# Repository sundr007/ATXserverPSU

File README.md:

# ATXserverPSU

ATX computer power supply utilizing redundant server power supplies for mining applications.
The Server power supplies will converter AC to 12Vdc with high efficiency.
The ATXs box will then take that 12V, create 5V and 3.3V, supply the needed logic and then provide a modular ATX connector set to connect to the mother board, graphics cards, etc.

The biggest benefit of this system is that the server power supplies will provide very high output power at high efficiency.

The circuit boards are done in KiCAD.
The mechanicals are done in OpenSCAD.

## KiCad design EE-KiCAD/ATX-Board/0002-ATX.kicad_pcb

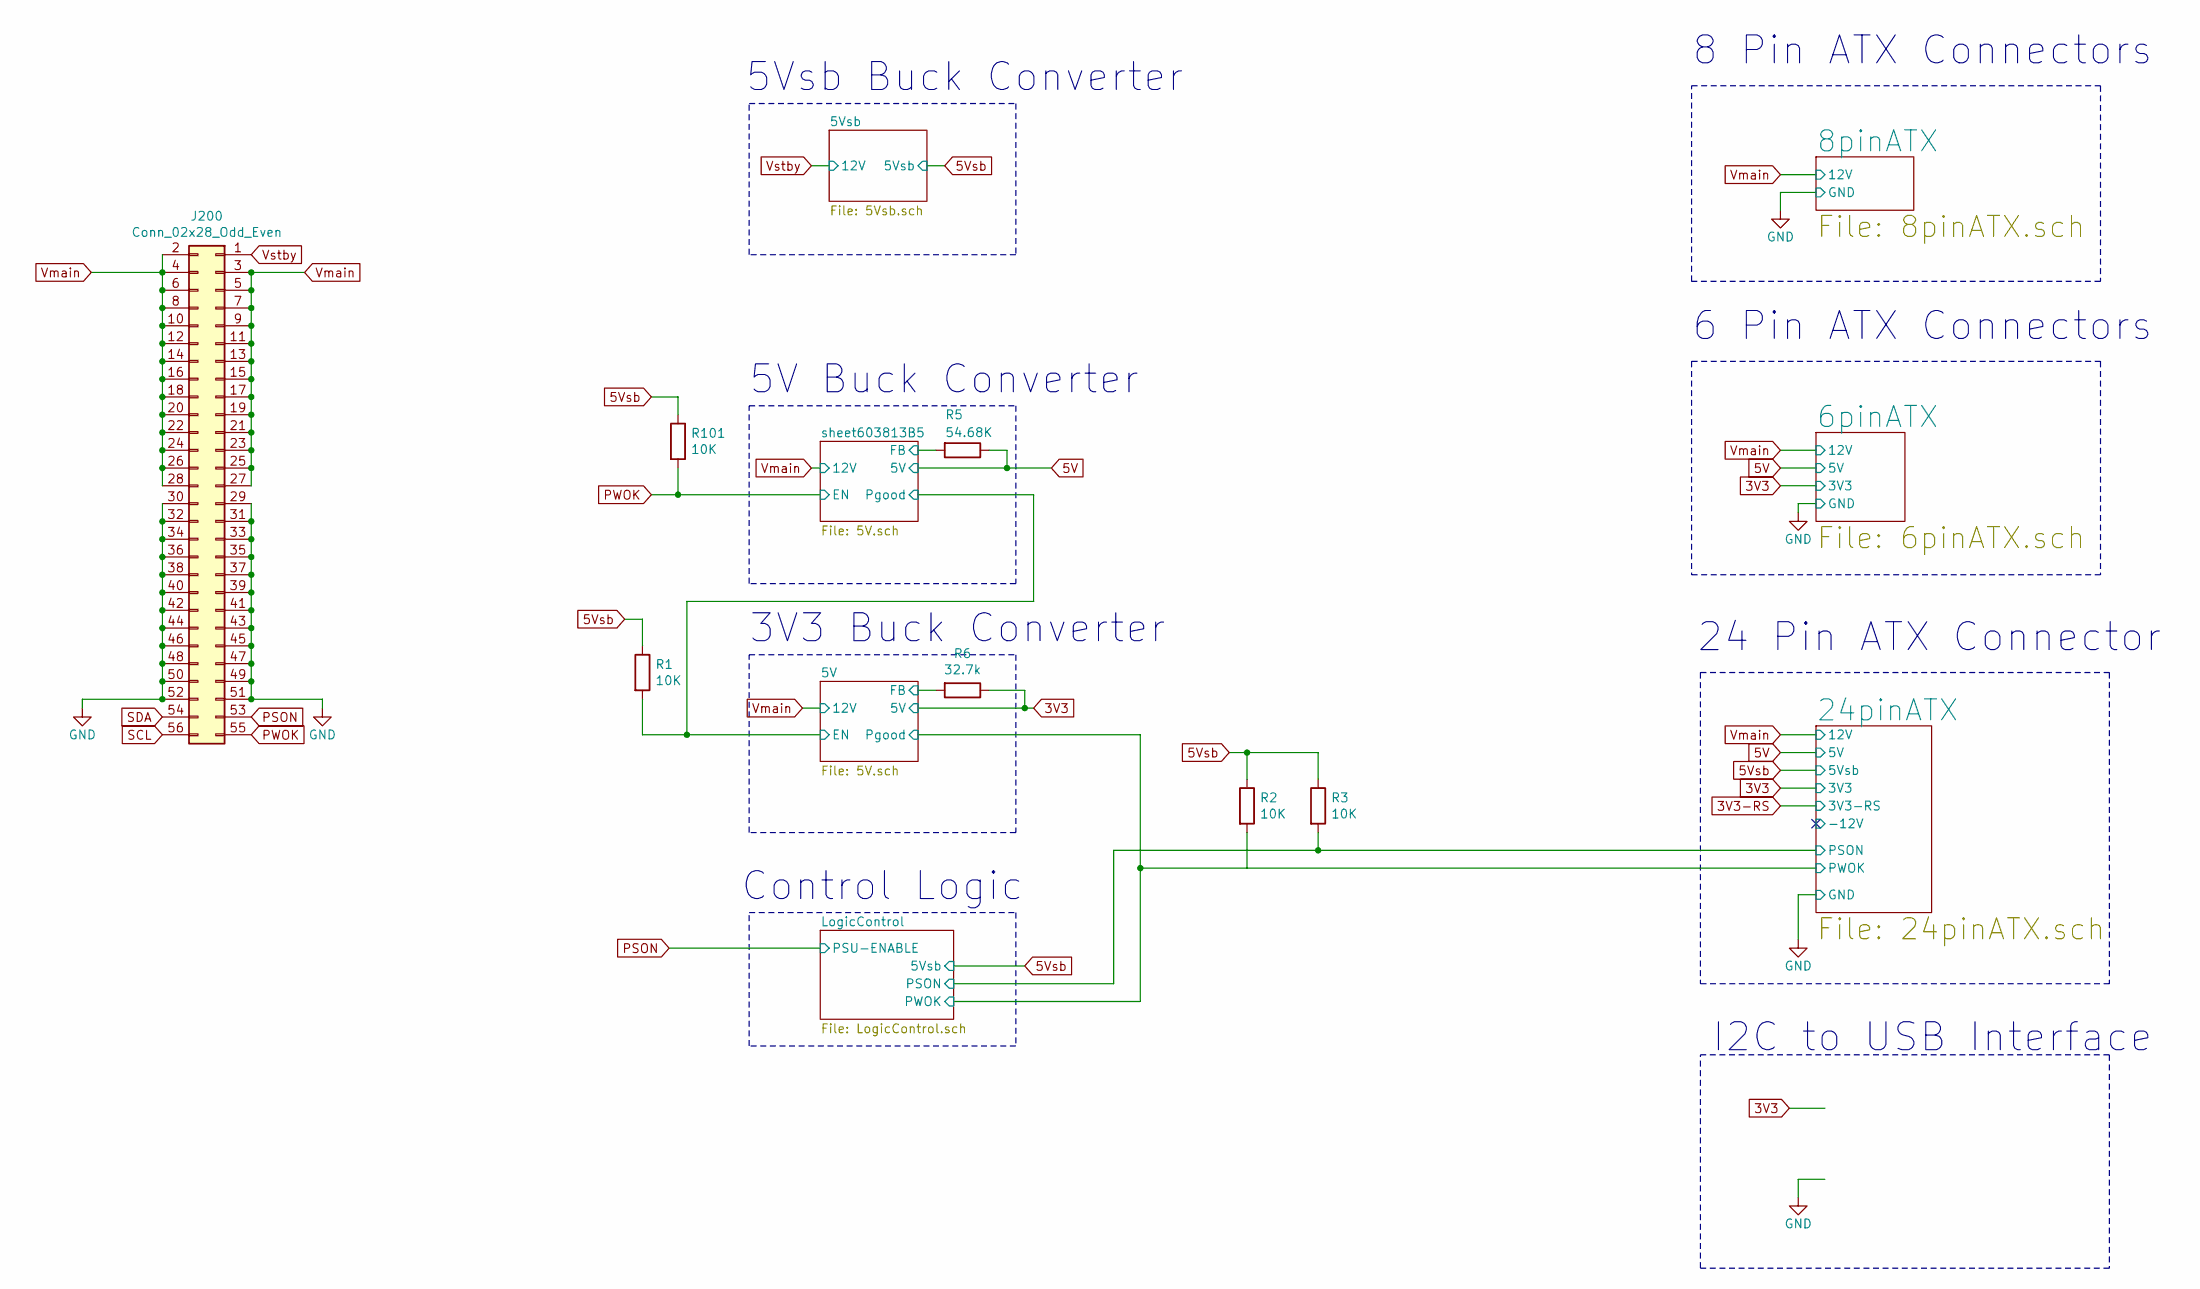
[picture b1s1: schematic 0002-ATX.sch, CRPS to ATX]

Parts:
J200: Conn_02x28_Odd_Even; PinSocket_2x28_P2.54mm_Horizontal
R1, R2, R3, R101: 10K; 0805_R
R5: 54.68K; 0805_R
R6: 32.7k; 0805_R

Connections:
3V3: R6.1; also elsewhere on the board
5V: R5.1; also elsewhere on the board
5Vsb: R1.1, R2.1, R3.1, R101.1; also elsewhere on the board
/5V/EN: R1.2; also elsewhere on the board
/5V/FB: R6.2; also elsewhere on the board
/24pinATX/PSON: R3.2; also elsewhere on the board
/sheet603813B5/FB: R5.2; also elsewhere on the board
GND: J200.29, J200.30, J200.31, J200.32, J200.33, J200.34, J200.35, J200.36, J200.37, J200.38, J200.39, J200.40, J200.41, J200.42, J200.43, J200.44, J200.45, J200.46, J200.47, J200.48, J200.49, J200.50, J200.51, J200.52; also elsewhere on the board
PSON: J200.53; also elsewhere on the board
PWOK: J200.55, R101.2; also elsewhere on the board
SCL: J200.56
SDA: J200.54
Vmain: J200.2, J200.3, J200.4, J200.5, J200.6, J200.7, J200.8, J200.9, J200.10, J200.11, J200.12, J200.13, J200.14, J200.15, J200.16, J200.17, J200.18, J200.19, J200.20, J200.21, J200.22, J200.23, J200.24, J200.25, J200.26, J200.27, J200.28; also elsewhere on the board
Vstby: J200.1; also elsewhere on the board

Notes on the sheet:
8 Pin ATX Connectors
6 Pin ATX Connectors
24 Pin ATX Connector
5Vsb Buck Converter
5V Buck Converter
3V3 Buck Converter
Control Logic
I2C to USB Interface

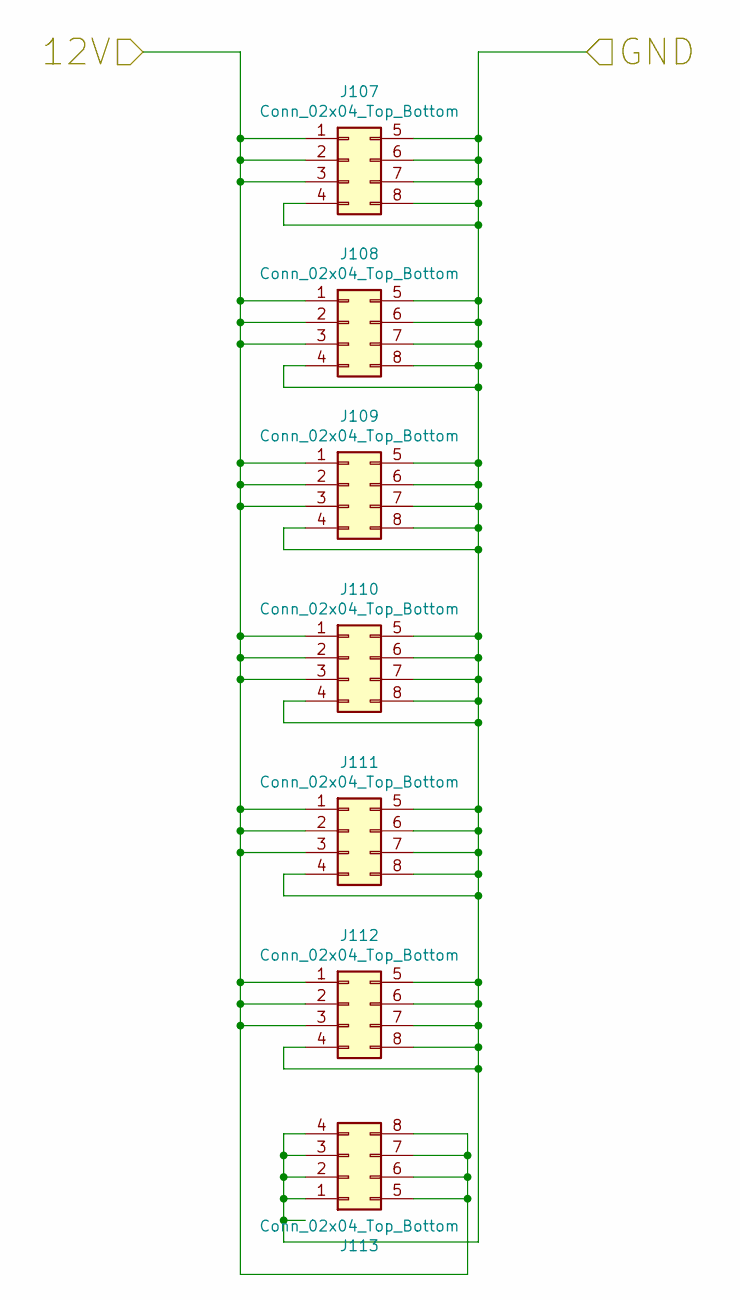
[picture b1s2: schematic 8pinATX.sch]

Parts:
J107, J108, J109, J110, J111, J112, J113: Conn_02x04_Top_Bottom; Molex_Mini-Fit_Jr_5566-08A_2x04_P4.20mm_Vertical

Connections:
GND: J107.4, J107.5, J107.6, J107.7, J107.8, J108.4, J108.5, J108.6, J108.7, J108.8, J109.4, J109.5, J109.6, J109.7, J109.8, J110.4, J110.5, J110.6, J110.7, J110.8, J111.4, J111.5, J111.6, J111.7, J111.8, J112.4, J112.5, J112.6, J112.7, J112.8, J113.1, J113.2, J113.3, J113.4; also elsewhere on the board
Vmain: J107.1, J107.2, J107.3, J108.1, J108.2, J108.3, J109.1, J109.2, J109.3, J110.1, J110.2, J110.3, J111.1, J111.2, J111.3, J112.1, J112.2, J112.3, J113.5, J113.6, J113.7, J113.8; also elsewhere on the board

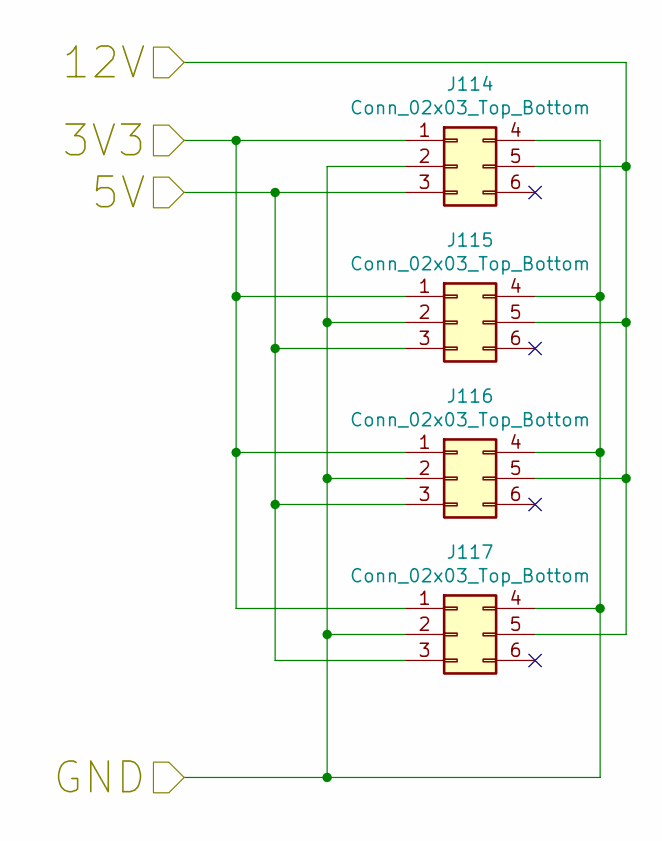
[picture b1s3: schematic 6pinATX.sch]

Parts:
J114, J115, J116, J117: Conn_02x03_Top_Bottom; Molex_Mini-Fit_Jr_5566-06A_2x03_P4.20mm_Vertical

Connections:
3V3: J114.1, J115.1, J116.1, J117.1; also elsewhere on the board
5V: J114.3, J115.3, J116.3, J117.3; also elsewhere on the board
GND: J114.2, J114.4, J115.2, J115.4, J116.2, J116.4, J117.2, J117.4; also elsewhere on the board
Vmain: J114.5, J115.5, J116.5, J117.5; also elsewhere on the board

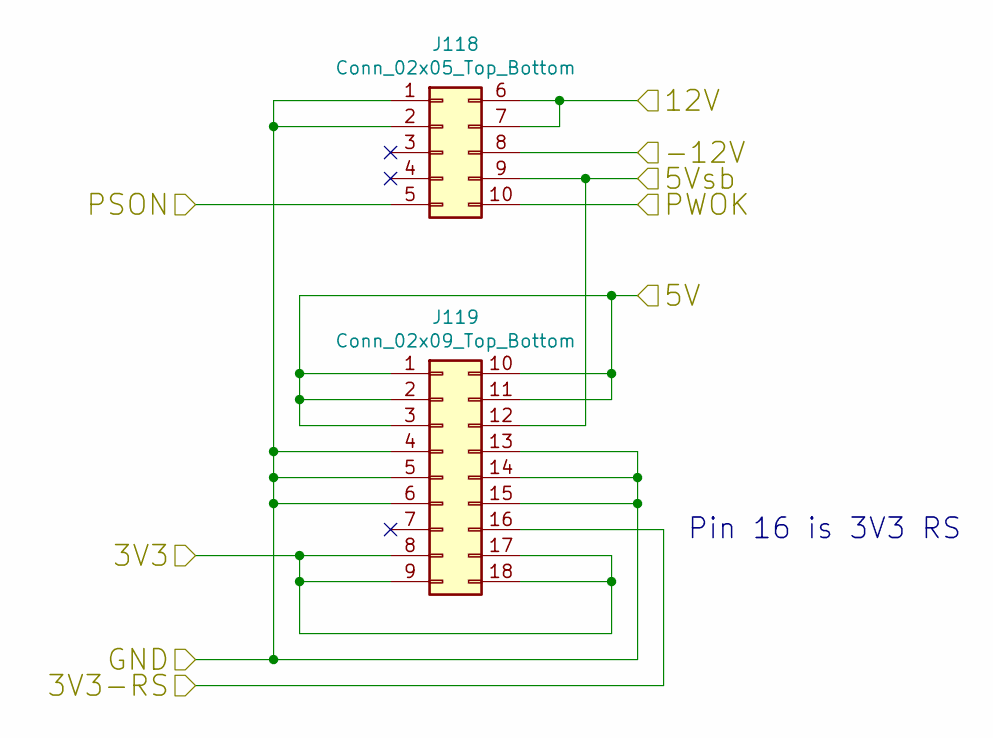
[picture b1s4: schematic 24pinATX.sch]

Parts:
J118: Conn_02x05_Top_Bottom; Molex_Mini-Fit_Jr_5566-10A_2x05_P4.20mm_Vertical
J119: Conn_02x09_Top_Bottom; Molex_Mini-Fit_Jr_5566-18A_2x09_P4.20mm_Vertical

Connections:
3V3: J119.8, J119.9, J119.17, J119.18; also elsewhere on the board
3V3-RS: J119.16
5V: J119.1, J119.2, J119.3, J119.10, J119.11; also elsewhere on the board
5Vsb: J118.9, J119.12; also elsewhere on the board
/24pinATX/-12V: J118.8
/24pinATX/PSON: J118.5; also elsewhere on the board
/24pinATX/PWOK: J118.10; also elsewhere on the board
GND: J118.1, J118.2, J119.4, J119.5, J119.6, J119.13, J119.14, J119.15; also elsewhere on the board
Vmain: J118.6, J118.7; also elsewhere on the board

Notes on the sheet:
Pin 16 is 3V3 RS

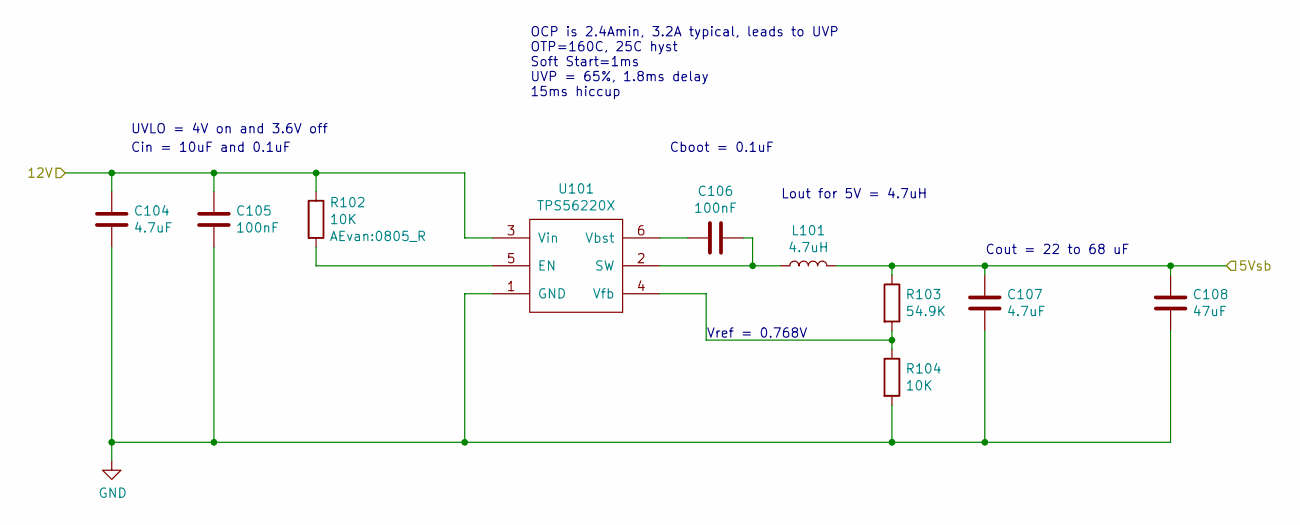
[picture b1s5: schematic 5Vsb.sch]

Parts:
C104, C107: 4.7uF; 0805_C
C105, C106: 100nF; 0805_C
C108: 47uF; CP_EIA-3528-15_AVX-H; Digikey_PN 718-2167-1-ND
L101: 4.7uH; L_6.3x6.3_H3
R102, R104: 10K; 0805_R
R103: 54.9K; 0805_R
U101: TPS56220X; SOT-23-6_Handsoldering

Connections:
5Vsb: C107.1, C108.1, L101.2, R103.1; also elsewhere on the board
GND: C104.2, C105.2, C107.2, C108.2, R104.2, U101.1 (GND); also elsewhere on the board
unnamed: C106.1, L101.1, U101.2 (SW)
unnamed: C106.2, U101.6 (Vbst)
unnamed: R102.2, U101.5 (EN)
unnamed: R103.2, R104.1, U101.4 (Vfb)
Vstby: C104.1, C105.1, R102.1, U101.3 (Vin); also elsewhere on the board

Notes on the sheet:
Cin = 10uF and 0.1uF
UVLO = 4V on and 3.6V off
Vref = 0.768V
Cboot = 0.1uF
Lout for 5V = 4.7uH
Cout = 22 to 68 uF
OCP is 2.4Amin, 3.2A typical, leads to UVP OTP=160C, 25C hyst Soft Start=1ms UVP = 65%, 1.8ms delay 15ms hiccup

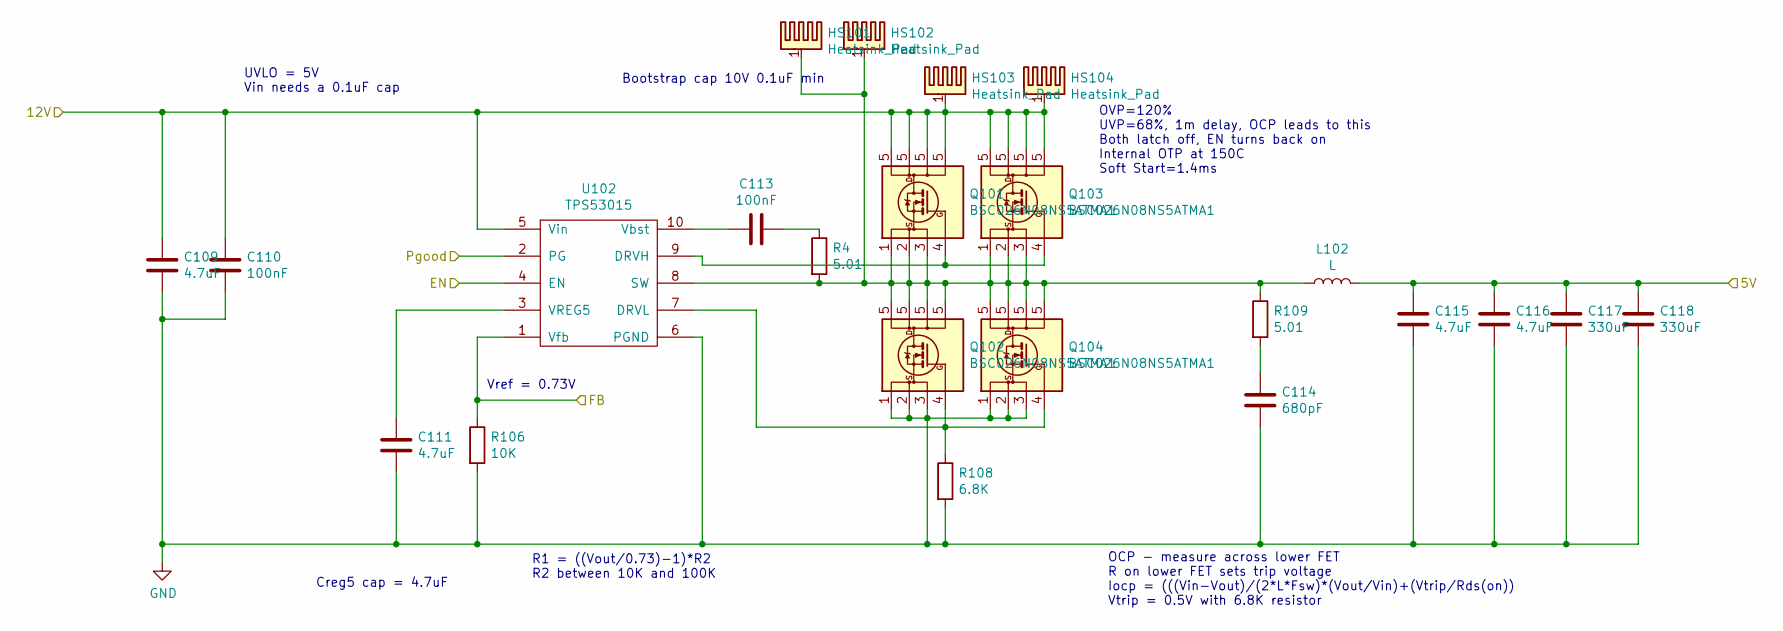
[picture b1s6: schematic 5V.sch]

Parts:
C109, C111, C115, C116: 4.7uF; 0805_C
C110, C113: 100nF; 0805_C
C114: 680pF; 0805_C
C117, C118: 330uF; C_Radial_D6.3mm_H7.0mm_P2.50mm
HS101, HS102, HS103, HS104: Heatsink_Pad; 5X6-HEATSINK
L102: L; L_12x12mm_H8mm
Q101, Q102, Q103, Q104: BSC026N08NS5ATMA1; TDSON-8-1
R4, R109: 5.01; 0805_R
R106: 10K; 0805_R
R108: 6.8K; 0805_R
U102: TPS53015; VSSOP-10_2.4x2.1mm_Pitch0.5mm

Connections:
3V3: C115.1, C116.1, C117.1, C118.1, L102.2; also elsewhere on the board
/5V/EN: U102.4 (EN); also elsewhere on the board
/5V/FB: R106.1, U102.1 (Vfb); also elsewhere on the board
/24pinATX/PWOK: U102.2 (PG); also elsewhere on the board
GND: C109.2, C110.2, C111.2, C114.2, C115.2, C116.2, C117.2, C118.2, Q102.1 (S), Q102.2 (S), Q102.3 (S), Q104.1 (S), Q104.2 (S), Q104.3 (S), R106.2, R108.2, U102.6 (PGND); also elsewhere on the board
unnamed: C111.1, U102.3 (VREG5)
unnamed: C113.1, R4.1
unnamed: C113.2, U102.10 (Vbst)
unnamed: C114.1, R109.2
unnamed: HS101.1, HS102.1, L102.1, Q101.1 (S), Q101.2 (S), Q101.3 (S), Q102.5 (D), Q103.1 (S), Q103.2 (S), Q103.3 (S), Q104.5 (D), R4.2, R109.1, U102.8 (SW)
unnamed: Q101.4 (G), Q103.4 (G), U102.9 (DRVH)
unnamed: Q102.4 (G), Q104.4 (G), R108.1, U102.7 (DRVL)
Vmain: C109.1, C110.1, HS103.1, HS104.1, Q101.5 (D), Q103.5 (D), U102.5 (Vin); also elsewhere on the board

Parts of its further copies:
C2, C4, C7, C8: 4.7uF; 0805_C
C3, C5: 100nF; 0805_C
C6: 680pF; 0805_C
C9, C10: 330uF; C_Radial_D6.3mm_H7.0mm_P2.50mm
HS1, HS2, HS3, HS4: Heatsink_Pad; 5X6-HEATSINK
L1: L; L_12x12mm_H8mm
Q1, Q2, Q3, Q4: BSC026N08NS5ATMA1; TDSON-8-1
R10: 10K; 0805_R
R11, R13: 5.01; 0805_R
R12: 6.8K; 0805_R
U1: TPS53015; VSSOP-10_2.4x2.1mm_Pitch0.5mm

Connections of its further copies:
5V: C7.1, C8.1, C9.1, C10.1, L1.2; also elsewhere on the board
/5V/EN: U1.2 (PG); also elsewhere on the board
/sheet603813B5/FB: R10.1, U1.1 (Vfb); also elsewhere on the board
GND: C2.2, C3.2, C4.2, C6.2, C7.2, C8.2, C9.2, C10.2, Q2.1 (S), Q2.2 (S), Q2.3 (S), Q4.1 (S), Q4.2 (S), Q4.3 (S), R10.2, R12.2, U1.6 (PGND); also elsewhere on the board
unnamed: C4.1, U1.3 (VREG5)
unnamed: C5.1, R11.1
unnamed: C5.2, U1.10 (Vbst)
unnamed: C6.1, R13.2
unnamed: HS1.1, HS2.1, L1.1, Q1.1 (S), Q1.2 (S), Q1.3 (S), Q2.5 (D), Q3.1 (S), Q3.2 (S), Q3.3 (S), Q4.5 (D), R11.2, R13.1, U1.8 (SW)
unnamed: Q1.4 (G), Q3.4 (G), U1.9 (DRVH)
unnamed: Q2.4 (G), Q4.4 (G), R12.1, U1.7 (DRVL)
PWOK: U1.4 (EN); also elsewhere on the board
Vmain: C2.1, C3.1, HS3.1, HS4.1, Q1.5 (D), Q3.5 (D), U1.5 (Vin); also elsewhere on the board

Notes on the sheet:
OVP=120% UVP=68%, 1m delay, OCP leads to this Both latch off, EN turns back on Internal OTP at 150C Soft Start=1.4ms
Bootstrap cap 10V 0.1uF min
UVLO = 5V Vin needs a 0.1uF cap
Creg5 cap = 4.7uF
R1 = ((Vout/0.73)-1)*R2 R2 between 10K and 100K
Vref = 0.73V
OCP - measure across lower FET R on lower FET sets trip voltage Iocp = (((Vin-Vout)/(2*L*Fsw)*(Vout/Vin)+(Vtrip/Rds(on)) Vtrip = 0.5V with 6.8K resistor

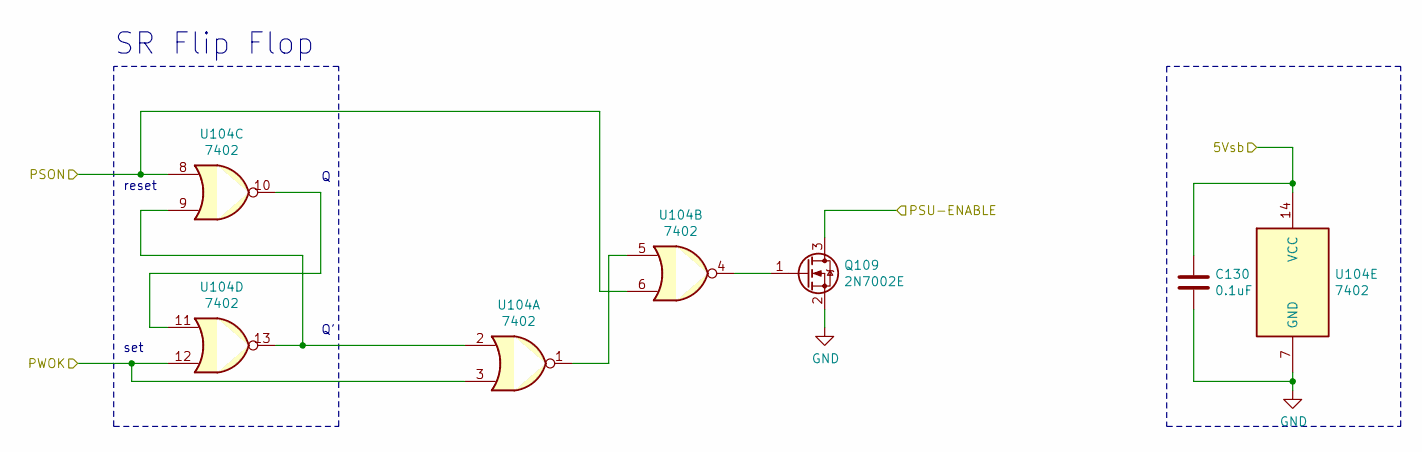
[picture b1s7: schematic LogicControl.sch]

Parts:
C130: 0.1uF; 0805_C
Q109: 2N7002E; SOT-23
U104: 7402; SOIC-14W_7.5x9mm_P1.27mm

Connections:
5Vsb: C130.1, U104.14 (VCC); also elsewhere on the board
/24pinATX/PSON: U104.6, U104.8; also elsewhere on the board
/24pinATX/PWOK: U104.3, U104.12; also elsewhere on the board
GND: C130.2, Q109.2 (S), U104.7 (GND); also elsewhere on the board
unnamed: Q109.1 (G), U104.4
unnamed: U104.1, U104.5
unnamed: U104.10, U104.11
unnamed: U104.2, U104.9, U104.13
PSON: Q109.3 (D); also elsewhere on the board

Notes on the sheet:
SR Flip Flop
set
reset

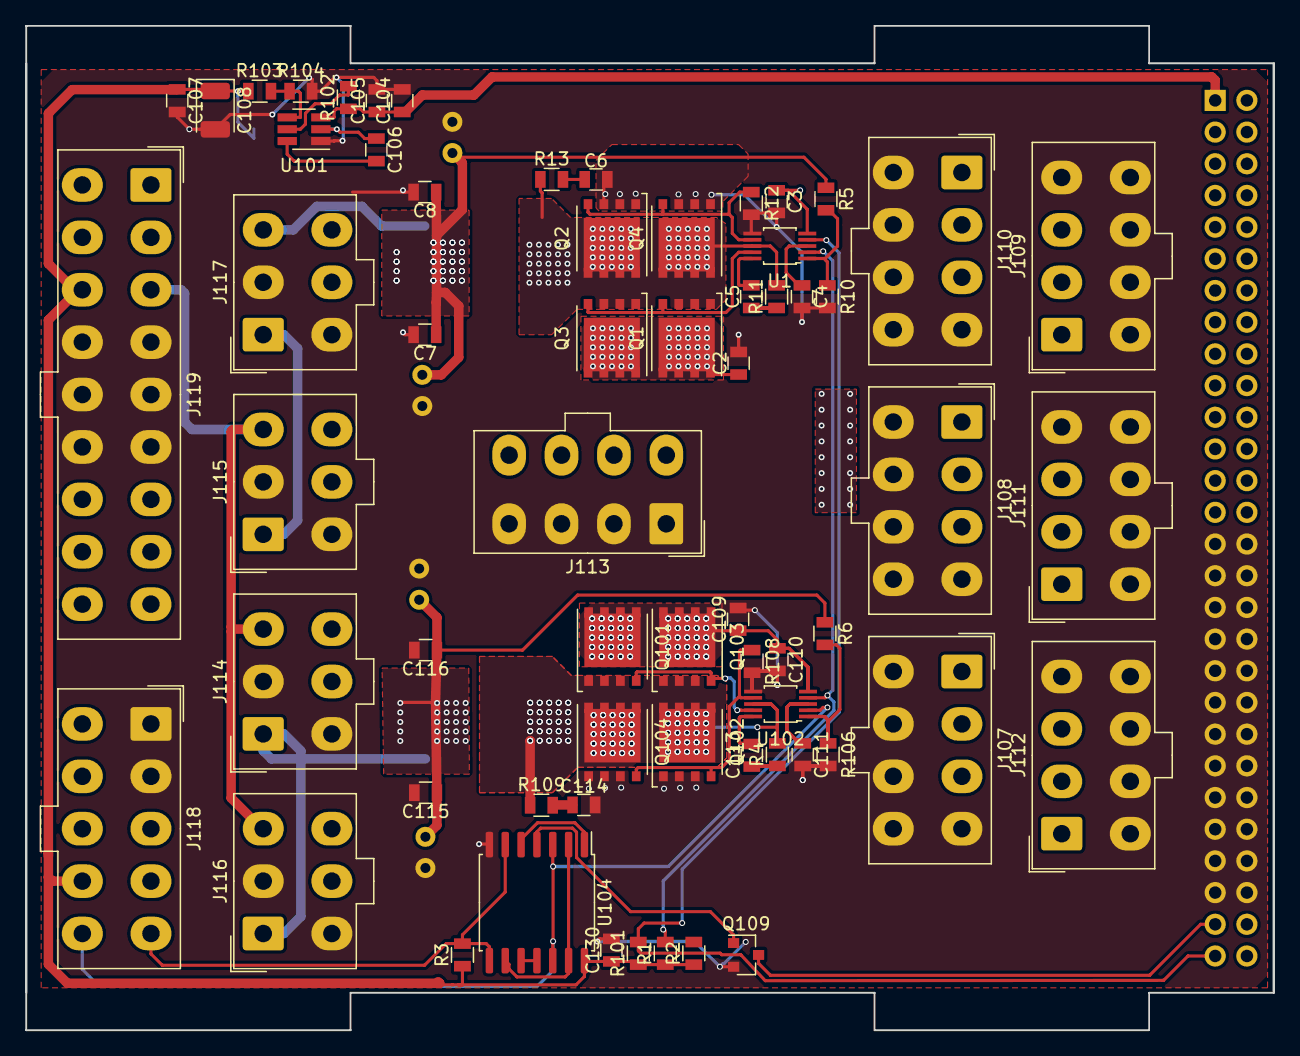
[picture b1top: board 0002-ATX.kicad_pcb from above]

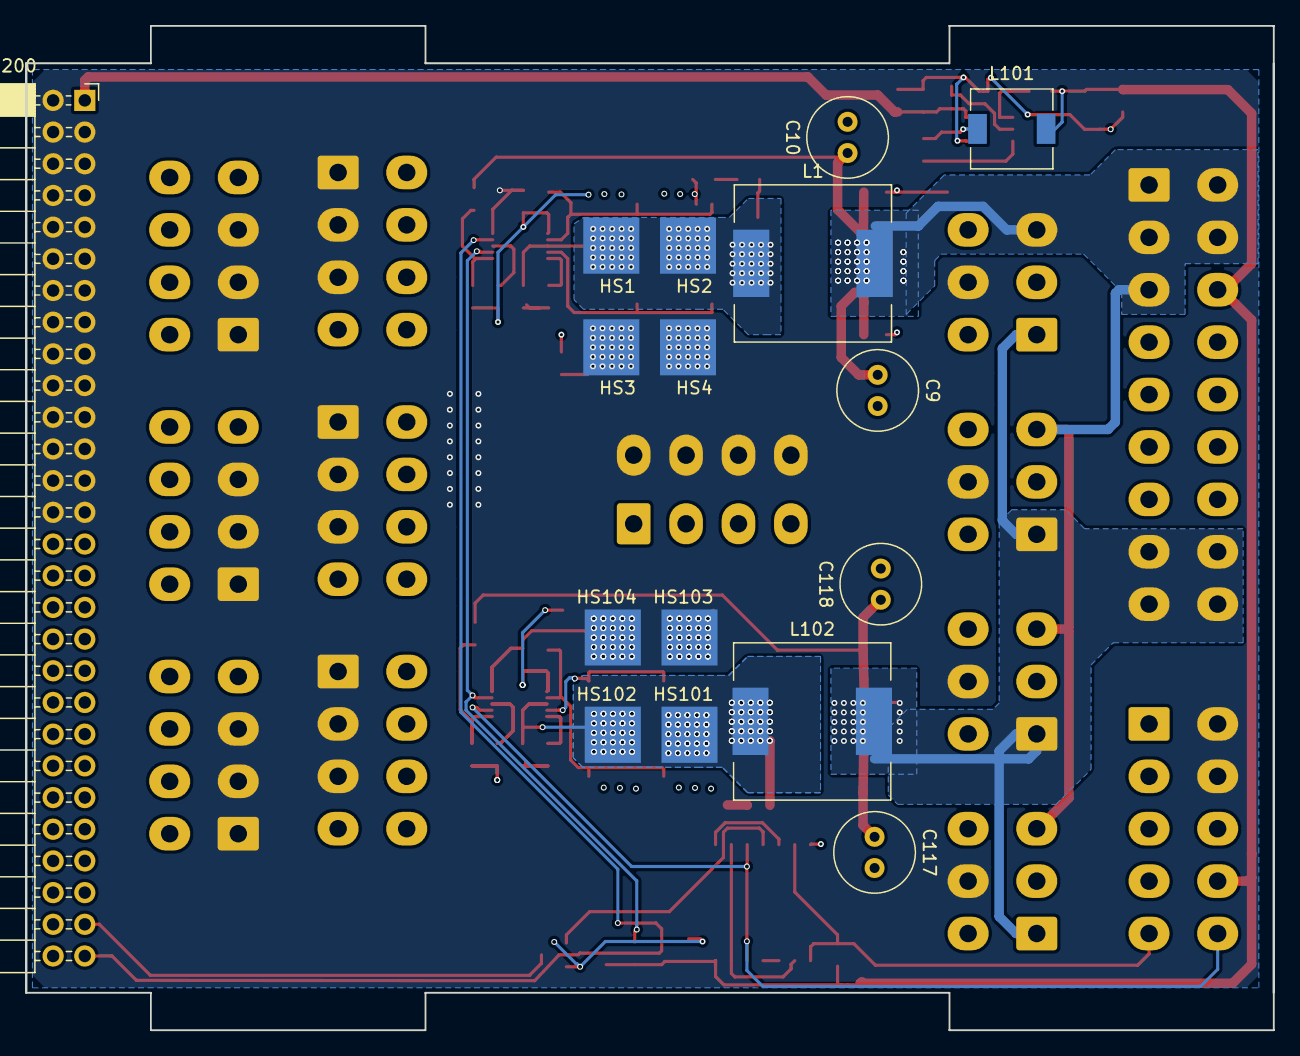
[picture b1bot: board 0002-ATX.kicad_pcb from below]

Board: 2 copper layers, 100.0 x 80.5 mm, 79 parts (16 on the bottom side), 35 nets.

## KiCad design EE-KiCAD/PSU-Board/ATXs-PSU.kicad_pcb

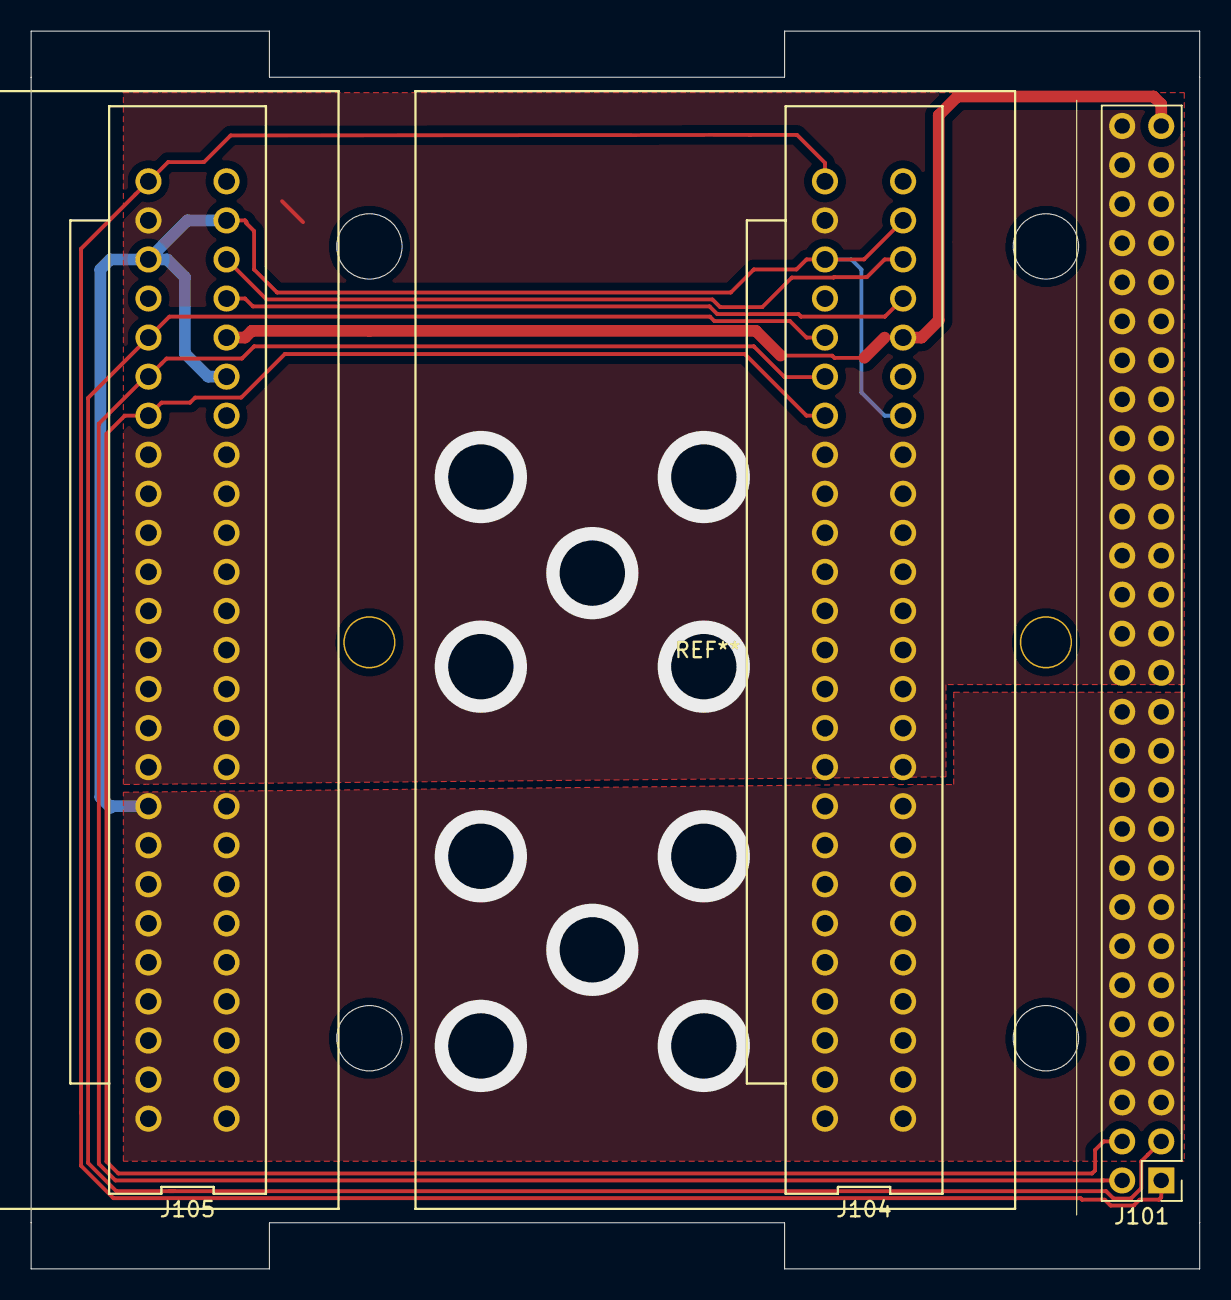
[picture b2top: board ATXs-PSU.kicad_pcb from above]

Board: 2 copper layers, 76.0 x 80.5 mm, 3 parts (0 on the bottom side), 9 nets.

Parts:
J101: Conn_02x28_Odd_Even; PinHeader_2x28_P2.54mm_Vertical
J104, J105: Conn_02x25_Row_Letter_First; CRPS_FCI_10035388-102LF

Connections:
/CRPS_PSU/CR_BUS: J104.b22, J105.b22
/CRPS_PSU/CurrentShare: J104.b23, J105.b23
GND: J101.5, J101.6, J101.7, J101.8, J101.9, J101.10, J101.11, J101.12, J101.13, J101.14, J101.15, J101.16, J101.17, J101.18, J101.19, J101.20, J101.21, J101.22, J101.23, J101.24, J101.25, J101.26, J104.a1, J104.a2, J104.a3, J104.a4, J104.a5, J104.a6, J104.a7, J104.a8, J104.a9, J104.a23, J104.b1, J104.b2, J104.b3, J104.b4, J104.b5, J104.b6, J104.b7, J104.b8, J104.b9, J104.b19, J104.b24, J105.a1, J105.a2, J105.a3, J105.a4, J105.a5, J105.a6, J105.a7, J105.a8, J105.a9, J105.a23, J105.b1, J105.b2, J105.b3, J105.b4, J105.b5, J105.b6, J105.b7, J105.b8, J105.b9, J105.b20, J105.b24
PSON: J101.3, J104.a21, J105.a21
PWOK: J101.1, J104.a25, J105.a25
SCL: J101.2, J104.a20, J105.a20
SDA: J101.4, J104.a19, J105.a19
Vmain: J101.27, J101.28, J101.29, J101.30, J101.31, J101.32, J101.33, J101.34, J101.35, J101.36, J101.37, J101.38, J101.39, J101.40, J101.41, J101.42, J101.43, J101.44, J101.45, J101.46, J101.47, J101.48, J101.49, J101.50, J101.51, J101.52, J101.53, J101.54, J101.56, J104.a10, J104.a11, J104.a12, J104.a13, J104.a14, J104.a15, J104.a16, J104.a17, J104.a18, J104.a24, J104.b10, J104.b11, J104.b12, J104.b13, J104.b14, J104.b15, J104.b16, J104.b17, J104.b18, J105.a10, J105.a11, J105.a12, J105.a13, J105.a14, J105.a15, J105.a16, J105.a17, J105.a18, J105.a24, J105.b10, J105.b11, J105.b12, J105.b13, J105.b14, J105.b15, J105.b16, J105.b17, J105.b18
Vstby: J101.55, J104.b21, J105.b21

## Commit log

2021-01-27 Add initial Mechanical Design
2021-01-28 Updates to mechanical Model. Add picture for github.
2021-01-28 add picture to README
2021-02-23 First draft of circuit boards, Updated Enclosure
2021-02-26 Finish first draft of PCBs. Pulled PCBs into OpenSCAD for fitment.
2021-03-05 Fitted PSUs into enclosure. Aligned PSU PCB.
2021-03-18 change pic
2021-05-05 add tabs on PCBs to set where they are in the box. Box adjustments.
